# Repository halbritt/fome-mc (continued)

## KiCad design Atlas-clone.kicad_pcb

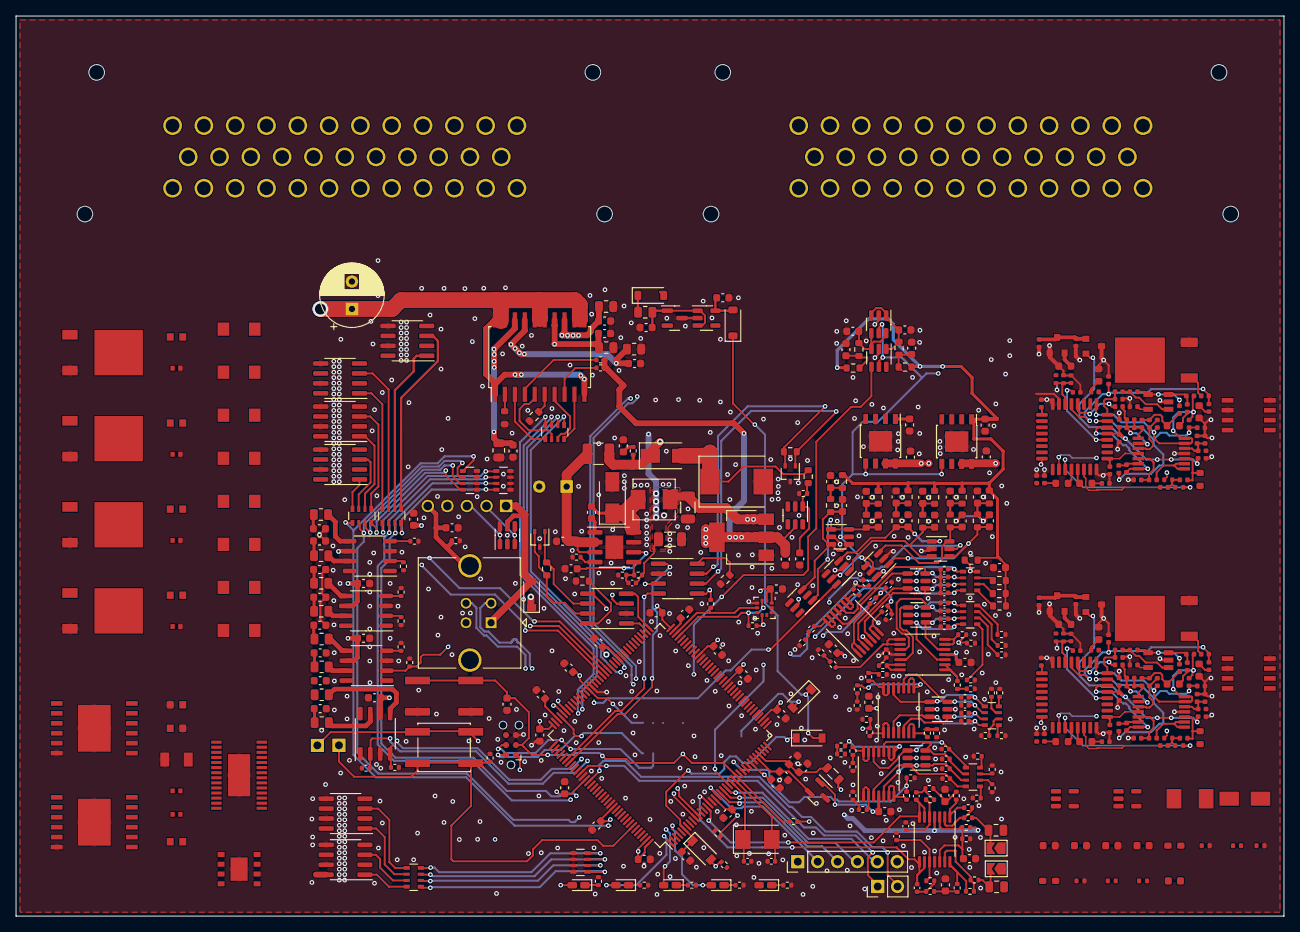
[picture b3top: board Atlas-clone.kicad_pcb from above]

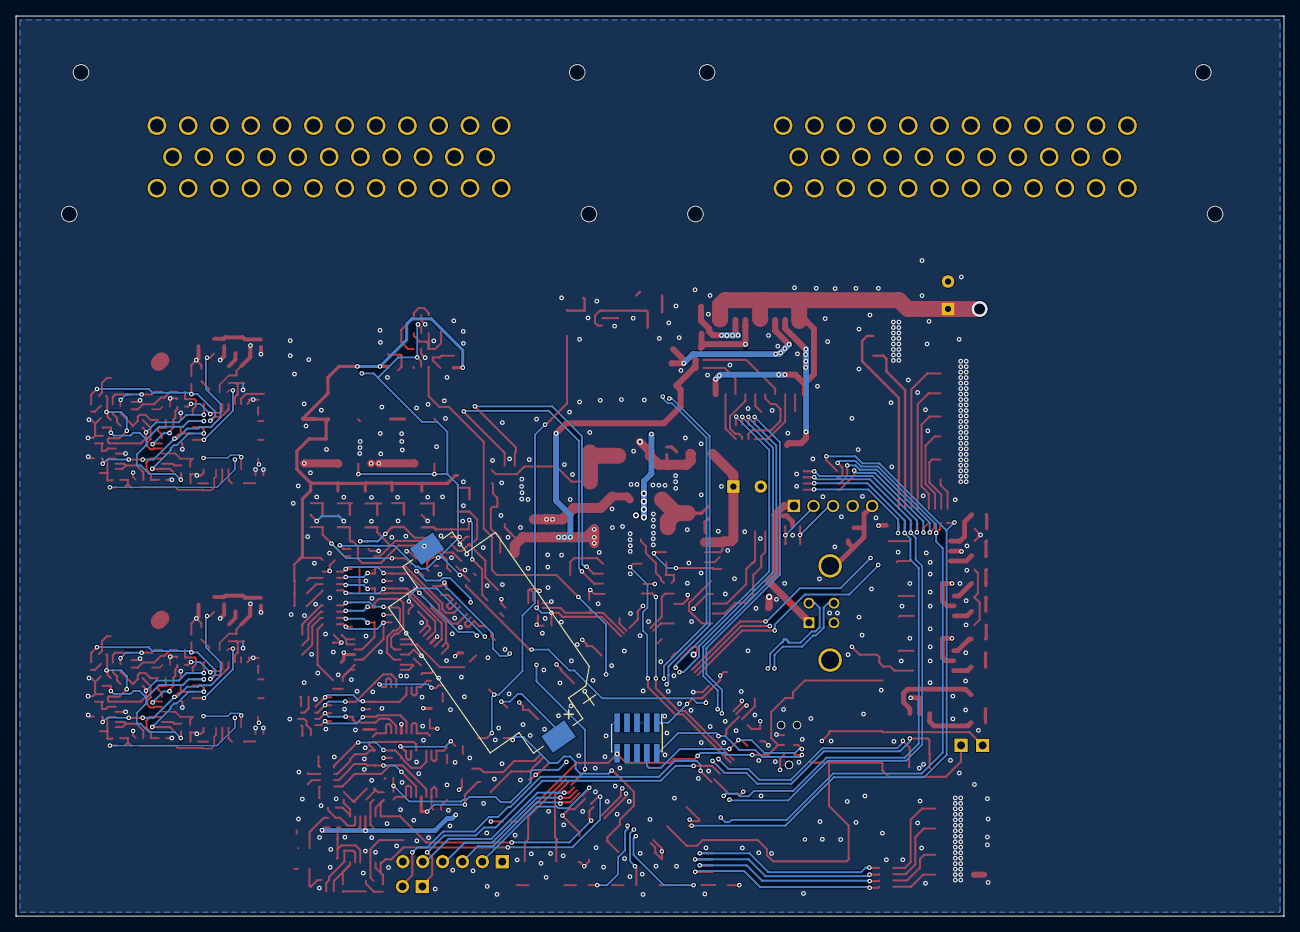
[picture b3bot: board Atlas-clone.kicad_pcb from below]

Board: 4 copper layers, 162.0 x 115.0 mm, 474 parts (2 on the bottom side), 353 nets.

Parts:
BT1: Battery_Cell; BatteryHolder_Keystone_1060_1x2032
C1, C6: 47u; CP_Elec_8x10.5
C2, C3, C5, C7, C9, C84: 1u; C_0603_1608Metric
C4, C14, C65, C66, C72, C76, C80, C82, C107, C310, C410: 4.7u; C_0603_1608Metric
C8, C15, C85, C86, C87, C88, C93, C94, C95, C96, C99, C100, C101, C102, C201, C202: 10n; C_0603_1608Metric
C10, C40, C41, C46, C51, C56, C61, C62, C63, C64, C67, C68, C69, C70, C71, C73, C79, C81, C83, C89, C91, C92, C97, C98, C103, C104, C105, C106: 100n; C_0603_1608Metric
C11, C20, C21: 330p; C_0402_1005Metric
C12, C13, C1201: 10u; C_1206_3216Metric
C16, C17: 3.3n; C_0805_2012Metric
C18, C19: 680p; C_0603_1608Metric
C22, C23: 47p; C_0402_1005Metric
C24, C25, C26, C27, C28, C29, C30, C31, C32, C33, C34, C35, C36, C37, C38, C39: 1n; C_0603_1608Metric
C42, C43, C44, C45, C47, C48, C49, C50, C52, C53, C54, C55, C57, C58, C59, C60, C302, C305, C308, C309, C311, C312, C313, C314, C316, C402, C405, C408, C409, C411, C412, C413, C414, C416: 100n; C_0402_1005Metric
C74, C75: 33p; C_0402_1005Metric
C77, C78, C90: 2.2u; C_0603_1608Metric
C301, C304, C306, C307, C317, C401, C404, C406, C407, C417: 1u; C_0402_1005Metric
C303, C403: 33n; C_0402_1005Metric
D1: SM15T33CA; D_SMC
D2, D3, D18: D_Schottky; D_SMA
D4, D5: PESD1CAN-UX; SOT-323_SC-70
D6, D7, D8, D14, D16, D17: schottky; D_SOD-123
D9, D12, D302, D402: GREEN; LED_0603_1608Metric
D10, D301, D304, D401, D404: RED; LED_0603_1608Metric
D11, D303, D403: BLUE; LED_0603_1608Metric
D13: ORANGE; LED_0603_1608Metric
D15: SRV05-4; SOT-23-6
D201, D202, D203, D204, D205, D206, D207, D208: B340A-13-F; D_SMA
FB1: Ferrite_Bead; L_0805_2012Metric
IC1: PSM712-LF-T7; SOT-23
J1: TE_776163-1; ampseal-35
J2: TE_776163-2; ampseal-35-2
J8: Conn_02x05_Odd_Even; PinHeader_2x05_P1.27mm_Vertical_SMD
J9: Conn_01x06; Tag-Connect_TC2030-IDC-NL_2x03_P1.27mm_Vertical
J11: Conn_01x06; PinHeader_1x06_P2.54mm_Vertical
J12: Conn_01x02; PinHeader_1x02_P2.54mm_Vertical
J13: USB_B; conn_5_2.5mm
J14: USB_B; USB_B_TE_5787834_Vertical
J15, J16: Conn_01x01; PinHeader_1x01_P2.54mm_Vertical
JP1, JP2: Jumper_NO_Small; SolderJumper-2_P1.3mm_Open_TrianglePad1.0x1.5mm
L1: 2.2u; L_1210_3225Metric
L2, L3: 10u; MWSA0503
Q201, Q202, Q203, Q204: FGD3040G2-F085; TO-252-2
Q301, Q401: VND14NV04; TO-252-2
R1, R3, R4, R47, R48, R49, R50, R59, R60, R61, R62, R71, R72, R73, R74, R83, R84, R85, R86, R89, R90, R97, R99, R100, R117, R118, R119, R121, R123, R205, R206, R207, R208, R209, R210, R303, R304, R311, R312, R321, R329, R333, R334, R403, R404, R411, R412, R421, R429, R433, R434: 10k; R_0402_1005Metric
R2: 1; R_0402_1005Metric
R5, R17, R18: 12k; R_0402_1005Metric
R6, R122, R331, R332, R431, R432: 68k; R_0402_1005Metric
R7, R8: 10; R_0603_1608Metric
R9, R10, R101, R102: 120; R_0603_1608Metric
R11, R12, R21, R22: 33k; R_0402_1005Metric
R13, R14, R19, R20, R98, R315, R317, R320, R415, R417, R420: 100k; R_0402_1005Metric
R15, R16, R51, R52, R53, R54, R63, R64, R65, R66, R75, R76, R77, R78: 470k; R_0402_1005Metric
R23, R24, R25, R26, R27, R28, R29, R30, R31, R32, R33, R34, R35, R36, R37, R38, R39, R40, R41, R42: 2.7k; R_0603_1608Metric
R43, R44, R45, R46, R55, R56, R57, R58, R67, R68, R69, R70, R79, R80, R81, R82: 5.6k; R_0402_1005Metric
R87, R88, R301, R302, R313, R318, R325, R326, R327, R330, R401, R402, R413, R418, R425, R426, R427, R430, R1501, R1502, R1503, R1504, R1601, R1602, R1603, R1604: 1k; R_0402_1005Metric
R91, R92, R93, R94, R95: 330; R_0402_1005Metric
R96, R116, R120: 82k; R_0603_1608Metric
R103, R104, R105, R106, R107: 4.7k; R_0805_2012Metric
R108, R109, R110, R111, R112, R113, R114, R115: 100; R_0805_2012Metric
R201, R202, R203, R204: 15R; R_0603_1608Metric
R212: 2.2k; R_0603_1608Metric
R305, R307, R405, R407: 27k; R_0402_1005Metric
R306, R406: 22k; R_0402_1005Metric
R308, R408: 47; R_0402_1005Metric
R309, R409: 10; R_0402_1005Metric
R310, R410: 61.9; R_0603_1608Metric
R314, R414: 62k; R_0603_1608Metric
R316, R416: 6.8k; R_0402_1005Metric
R319, R419: 47k; R_0402_1005Metric
R324, R424: 3.3k; R_0402_1005Metric
RN1, RN2, RN3, RN4, RN11: 10k; R_Array_Convex_4x0603
RN5, RN6, RN7, RN8, RN9, RN10: 1k; R_Array_Convex_4x0603
SW1, SW2: SW_Push; SW_SPST_EVQQ2
U1, U2: TLS115D0E; Infineon_PG-DSO-8-43
U3: LMR14020; SOIC-8-1EP_3.9x4.9mm_P1.27mm_EP2.29x3mm
U4, U5: MCP2551-I-SN; SOIC-8_3.9x4.9mm_P1.27mm
U6: AMS1117-3.3; SOT-223-3_TabPin2
U7, U15, U17, U19, U21, U301, U401: MCP6004; TSSOP-14_4.4x5mm_P0.65mm
U8, U9, U10, U14: SN74LVC2G17DB; SOT-23-6
U11, U12, U13, U16, U18, U20, U22: SRV05-4; SOT-23-6
U23: REF3333; SOT-23
U24: LPS25HB; ST_HLGA-10_2.5x2.5mm_P0.6mm_LayoutBorder3x2y
U25: XTSD04GLGEAG; LGA-8_6x8mm_P1.25mm
U26: STM32H753ZIT6; LQFP-144_20x20mm_P0.5mm
U27: USBLC6-2SC6; SOT-23-6
U28: S3225SMD32.768KOSC; SOT-23-5
U40: BTS716G; Infineon_PG-DSO-20-32
U41: MIC5205-3.3YM5; SOT-23-5
U42, U43, U44, U45: MIC4427; SO-8_3.9x4.9mm_P1.27mm
U46: LM2733XMFX/NOPB; SOT-23-5
U201, U203: TLE9201SG; Infineon_PG-DSO-12-9
U202: DRV8825PWPR; HTSSOP-28-1EP_4.4x9.7mm_P0.65mm_EP2.85x5.4mm
U302, U402: STM32F042K6Tx; LQFP-32_7x7mm_P0.8mm
U303, U403: REF3033; SOT-23
U305, U405: AD8628; TSOT-23-5
U307, U407: TJA1051T-3; SOIC-8_3.9x4.9mm_P1.27mm
U309, U409: XC6206P332MR; SOT-23
U1001, U1002, U1101, U1102, U1201, U1202: VNLD5090; SOIC-8_3.9x4.9mm_P1.27mm
Y1: 8MHz; Crystal_SMD_5032-2Pin_5.0x3.2mm

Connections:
+3.3V: R210.2, U201.2, U202.12, U202.16, U203.2
+3V3: C14.1, C61.2, C62.2, C63.1, C64.2, C65.2, C66.2, C67.2, C68.2, C69.2, C71.2, C72.2, C73.2, C76.2, D8.2 (A), D9.2 (A), D15.5 (VP), FB1.1, J8.1, J9.1, J11.1, J15.1, R1.2, R4.2, R11.2, R87.1, R88.1, R89.2, R99.2, R100.2, SW2.2, U4.5 (Vref), U5.5 (Vref), U6.2 (VO), U7.4 (V+), U24.1 (VDDio), U24.6 (~CS), U24.10 (VDD), U25.4, U26.17 (VDD), U26.30 (VDD), U26.39 (VDD), U26.52 (VDD), U26.62 (VDD), U26.72 (VDD), U26.84 (VDD), U26.95 (VDDUSB), U26.108 (VDD), U26.121 (VDDSDMMC), U26.131 (VDD), U26.143 (PDR_ON), U26.144 (VDD)
+3V3_WBO1: C305.1, C310.1, C312.1, C313.1, C314.1, R314.1, R318.2, U301.4 (V+), U302.1 (VDD), U302.17 (VDDIO2), U305.5 (V+), U309.2 (VO)
+3V3_WBO2: C405.1, C410.1, C412.1, C413.1, C414.1, R414.1, R418.2, U401.4 (V+), U402.1 (VDD), U402.17 (VDDIO2), U405.5 (V+), U409.2 (VO)
+5V: C11.1, C12.1, C13.1, C40.1, C46.1, C51.1, C56.1, C91.2, C92.2, C97.2, C98.2, C308.1, C317.1, C408.1, C417.1, D14.1 (K), L2.2, R6.2, U1.5 (ADJ), U2.5 (ADJ), U4.3 (VDD), U5.3 (VDD), U6.3 (VI), U8.5 (VCC), U9.5 (VCC), U10.5 (VCC), U11.5 (VP), U12.5 (VP), U13.5 (VP), U14.5 (VCC), U15.4 (V+), U16.5 (VP), U17.4 (V+), U18.5 (VP), U19.4 (V+), U20.5 (VP), U21.4 (V+), U22.5 (VP), U23.1 (IN), U42.6 (V+), U43.6 (V+), U44.6 (V+), U45.6 (V+), U303.1 (IN), U307.3, U309.3 (VI), U403.1 (IN), U407.3, U409.3 (VI)
/5V_SENSOR_1: C3.1, C41.2, J1.29, R23.1, R24.1, R25.1, R26.1, R27.1, R28.1, R35.1, R36.1, R39.1, R40.1, R41.1, R42.1, R118.1, U1.1 (OUT)
/5V_SENSOR_2: C9.1, J1.30, U2.1 (OUT)
/12V_MR: C1.1, C1201.2, D201.1, D202.1, D203.1, D204.1, D205.1, D206.1, D207.1, D208.1, J1.24, J1.27, R116.1, R212.1, R320.1, R420.1, U40.1 (VBB), U40.10 (VBB), U40.11 (VBB), U40.12 (VBB), U40.15 (VBB), U40.16 (VBB), U40.19 (VBB), U40.20 (VBB), U201.4, U202.11, U203.4
/12V_PROT: C2.1, C5.1, D2.1 (K), L1.1, R2.1, U1.7 (EN), U1.8 (IN), U2.7 (EN), U2.8 (IN)
/12V_RAW: D1.1 (A1), D2.2 (A), J1.26, R96.1
/AT1: J2.1, R39.2, RN1.1 (R1.1)
/AT2: J2.2, R40.2, RN1.2 (R2.1)
/AT3: R41.2, RN1.3 (R3.1)
/AT4: R42.2, RN1.4 (R4.1)
/AV1: J2.5, R51.1, RN2.1 (R1.1)
/AV2: J2.3, R52.1, RN2.2 (R2.1)
/AV3: J2.6, R53.1, RN2.3 (R3.1)
/AV4: J2.4, R54.1, RN2.4 (R4.1)
/AV5: J2.7, R63.1, RN3.1 (R1.1)
/AV6: J2.8, R64.1, RN3.2 (R2.1)
/AV7: R65.1, RN3.3 (R3.1)
/AV8: R66.1, RN3.4 (R4.1)
/AV9: R75.1, RN4.1 (R1.1)
/AV10: R76.1, RN4.2 (R2.1)
/AV11: R77.1, RN4.3 (R3.1)
/BOOT0_NET: J16.1, R90.1, R209.2, SW2.1, U26.138 (BOOT0)
/CAN2+: D5.2 (A2), R10.1, U5.7 (CANH), U307.7, U407.7
/CAN2-: D5.1 (A1), R10.2, U5.6 (CANL), U307.6, U407.6
/CAN+: D4.2 (A2), J2.28, R9.1, U4.7 (CANH)
/CAN-: D4.1 (A1), J2.29, R9.2, U4.6 (CANL)
/DIGITAL_1: C24.1, J2.16, R23.2, R29.2
/DIGITAL_2: C25.1, J2.15, R24.2, R30.2
/DIGITAL_3: C26.1, J2.18, R25.2, R31.2
/DIGITAL_4: C27.1, J2.17, R26.2, R32.2
/DIGITAL_5: C28.1, R27.2, R33.2
/DIGITAL_6: C29.1, R28.2, R34.2
/ETB1_DIR: U26.79 (PD10), U201.1
/ETB1_DIS: R210.1, U26.80 (PD11), U201.11
/ETB1_OUT+: C201.2, J1.15, U201.5
/ETB1_OUT-: C202.1, J1.16, U201.7
/ETB1_PWM: U26.81 (PD12), U201.12
/ETB2_DIR: U26.78 (PD9), U203.1
/ETB2_DIS: U26.77 (PD8), U203.11
/ETB2_OUT+: J1.17, U203.5
/ETB2_OUT-: J1.18, U203.7
/ETB2_PWM: U26.82 (PD13), U203.12
/HS1: C85.1, J1.14, R103.1, U40.18 (OUT1)
/HS2: C86.1, R104.1, U40.17 (OUT2)
/HS3: C87.1, R105.1, U40.14 (OUT3)
/HS4: C88.1, R106.1, U40.13 (OUT4)
/IGN1: C93.1, R108.1, R201.1
/IGN1_COIL: J1.6, Q201.2
/IGN2: C94.1, R109.1, R202.1
/IGN2_COIL: J1.7, Q202.2
/IGN3: C95.1, R110.1, R203.1
/IGN3_COIL: J1.8, Q203.2
/IGN4: C96.1, R111.1, R204.1
/IGN4_COIL: J1.9, Q204.2
/IGN5: C99.1, J2.23, R112.1
/IGN6: C100.1, J2.24, R113.1
/IGN7: C101.1, J2.25, R114.1
/IGN8: C102.1, J2.26, R115.1
/IGN10: J12.2, U26.122 (PD6)
/IGN11: J12.1, U26.119 (PD5)
/KNOCK_1: C16.2, J2.9, JP1.1
/KNOCK_2: C17.2, J2.10, JP2.1
/Keep_Alive/Keep_Alive: D6.1 (K), D7.2 (A), D17.1 (K)
/LS1: D201.2, J1.1, U1001.6 (D2)
/LS2: D202.2, J1.2, U1001.8 (D1)
/LS3: D203.2, J1.3, U1002.6 (D2)
/LS4: D204.2, J1.4, U1002.8 (D1)
/LS5: D205.2, J1.10, U1101.6 (D2)
/LS6: D206.2, J1.11, U1101.8 (D1)
/LS7: D207.2, J1.12, U1102.6 (D2)
/LS8: D208.2, J1.13, U1102.8 (D1)
/LS9: U26.134 (PB4), U202.22
/LS12: U26.137 (PB7), U202.20
/LS14: J2.27, R212.2, U1201.8 (D1)
/PB8_STEP_EN: RN9.8 (R1.2), RN10.4 (R4.1), U26.139 (PB8), U202.21
/Perm_Live: D16.2 (A), J1.28
/RC2: J1.35, R209.1, U26.101 (PA9)
/STEP_1A: J1.19, U202.4
/STEP_1B: J1.20, U202.6
/STEP_2A: J1.21, U202.9
/STEP_2B: J1.22, U202.7
/USB_D+: J2.34, J13.3, J14.3, U26.104 (PA12), U27.1 (I/O1), U27.6 (I/O1)
/USB_D-: J2.35, J13.2, J14.2, U26.103 (PA11), U27.3 (I/O2), U27.4 (I/O2)
/USB_SHIELD: C83.1, J13.5, J14.5, R98.1
/VBOOST: C6.1, C7.1, L1.2, R120.1, U3.2 (VIN), U3.3 (EN)
/VR1+: C37.1, J2.11, R36.2, R38.2
/VR2+: C36.1, J2.13, R35.2, R37.2
/WBO1_BOOT0: R329.2, U26.2 (PE3), U302.31 (PB8)
/WBO1_H-: J1.23, Q301.2 (D)
/WBO1_IP: J2.20, R310.2, R312.2
/WBO1_NRST: C316.1, U26.1 (PE2), U302.4 (NRST)
/WBO1_RTRIM: J2.21, R308.1, R310.1, R311.2, R334.1
/WBO1_UN: C302.1, J2.22, R314.2, U301.10 (+)
/WBO1_VM: C304.1, J2.19, R303.1, R309.1, U302.7 (PA1)
/WBO2_BOOT0: R429.2, U26.4 (PE5), U402.31 (PB8)
/WBO2_H-: J1.25, Q401.2 (D)
/WBO2_IP: J2.31, R410.2, R412.2
/WBO2_NRST: C416.1, U26.3 (PE4), U402.4 (NRST)
/WBO2_RTRIM: J2.32, R408.1, R410.1, R411.2, R434.1
/WBO2_UN: C402.1, J2.33, R414.2, U401.10 (+)
/WBO2_VM: C404.1, J2.30, R403.1, R409.1, U402.7 (PA1)
/highside_quad/IN1: RN11.4 (R4.1), U26.89 (PG4)
/highside_quad/IN2: RN11.3 (R3.1), U26.88 (PG3)
/highside_quad/IN3: RN11.2 (R2.1), U26.87 (PG2)
/highside_quad/IN4: RN11.1 (R1.1), U26.86 (PD15)
/ign1/IN1: R1501.2, U26.133 (PB3), U42.2 (IN_A)
/ign1/IN2: R1502.2, U26.132 (PG15), U42.4 (IN_B)
/ign1/IN3: R1503.2, U26.129 (PG14), U43.2 (IN_A)
/ign1/IN4: R1504.2, U26.128 (PG13), U43.4 (IN_B)
/ign2/IN1: R1601.2, U26.127 (PG12), U44.2 (IN_A)
/ign2/IN2: R1602.2, U26.126 (PG11), U44.4 (IN_B)
/ign2/IN3: R1603.2, U26.125 (PG10), U45.2 (IN_A)
/ign2/IN4: R1604.2, U26.124 (PG9), U45.4 (IN_B)
/knock/FILTERED_1: C20.2, U7.6 (-), U7.7, U26.14 (PF4)
/knock/FILTERED_2: C21.2, U7.8, U7.9 (-), U26.15 (PF5)
/knock/V_mid: C15.2, R11.1, R12.1, U7.3 (+), U7.12 (+)
/lowside_quad1/IN1: RN5.8 (R1.2), RN6.4 (R4.1), U26.90 (PG5)
/lowside_quad1/IN2: RN5.7 (R2.2), RN6.3 (R3.1), U26.91 (PG6)
/lowside_quad1/IN3: RN5.6 (R3.2), RN6.2 (R2.1), U26.92 (PG7)
/lowside_quad1/IN4: RN5.5 (R4.2), RN6.1 (R1.1), U26.93 (PG8)
/lowside_quad2/IN1: RN7.8 (R1.2), RN8.4 (R4.1), U26.96 (PC6)
/lowside_quad2/IN2: RN7.7 (R2.2), RN8.3 (R3.1), U26.97 (PC7)
/lowside_quad2/IN3: RN7.6 (R3.2), RN8.2 (R2.1), U26.110 (PA15)
/lowside_quad2/IN4: RN7.5 (R4.2), RN8.1 (R1.1), U26.117 (PD3)
/lowside_quad4/IN2: RN9.7 (R2.2), RN10.3 (R3.1), U26.140 (PB9)
/lowside_quad4/IN3: RN9.6 (R3.2), RN10.2 (R2.1), U26.141 (PE0)
/lowside_quad4/IN4: RN9.5 (R4.2), RN10.1 (R1.1), U26.142 (PE1)
/mcu/5V_SENSE_DIVIDED: C104.1, R118.2, R119.1, U26.50 (PF12)
/mcu/5V_SENSOR_1_PG: R1.1, U1.4 (PG), U26.55 (PF15)
/mcu/5V_SENSOR_2_PG: R4.1, U2.4 (PG), U26.54 (PF14)
/mcu/12V_DIVIDED: C84.1, D15.1 (IO1), R96.2, R97.1, U26.45 (PC5)
/mcu/AT1: R43.1, R47.2, U26.27 (PC1)
/mcu/AT2: R44.1, R48.2, U26.28 (PC2)
/mcu/AT3: R45.1, R49.2, U26.29 (PC3)
/mcu/AT4: R46.1, R50.2, U26.44 (PC4)
/mcu/AUX_SPI_CS: J11.2, U26.18 (PF6)
/mcu/AUX_SPI_MISO: J11.4, U26.20 (PF8)
/mcu/AUX_SPI_MOSI: J11.5, U26.21 (PF9)
/mcu/AUX_SPI_SCK: J11.3, U26.19 (PF7)
/mcu/AV1: R55.1, R59.2, U26.34 (PA0)
/mcu/AV2: R56.1, R60.2, U26.35 (PA1)
/mcu/AV3: R57.1, R61.2, U26.36 (PA2)
/mcu/AV4: R58.1, R62.2, U26.37 (PA3)
/mcu/AV5: R67.1, R71.2, U26.40 (PA4)
/mcu/AV6: R68.1, R72.2, U26.41 (PA5)
/mcu/AV7: R69.1, R73.2, U26.42 (PA6)
/mcu/AV8: R70.1, R74.2, U26.43 (PA7)
/mcu/AV9: R79.1, R83.2, U26.46 (PB0)
/mcu/AV10: R80.1, R84.2, U26.47 (PB1)
/mcu/AV11: R81.1, R85.2, U26.26 (PC0)
/mcu/BARO_SCL: R88.2, U24.2 (SCL/SCLK), U26.69 (PB10)
/mcu/BARO_SDA: R87.2, U24.4 (SDA/MOSI), U26.70 (PB11)
/mcu/CAN2_RX: U5.4 (RXD), U26.73 (PB12)
/mcu/CAN2_TX: U5.1 (TXD), U26.74 (PB13)
/mcu/CAN_RX: U4.4 (RXD), U26.114 (PD0)
/mcu/CAN_TX: U4.1 (TXD), U26.115 (PD1)
/mcu/DIGITAL1: U10.6, U26.56 (PG0)
/mcu/DIGITAL2: U8.6, U26.57 (PG1)
/mcu/DIGITAL3: U8.4, U26.63 (PE10)
/mcu/DIGITAL4: U9.6, U26.64 (PE11)
/mcu/DIGITAL5: U10.4, U26.65 (PE12)
/mcu/DIGITAL6: U9.4, U26.66 (PE13)
/mcu/LED1: D10.2 (A), U26.10 (PF0)
/mcu/LED2: D11.2 (A), U26.12 (PF2)
/mcu/LED3: D12.2 (A), U26.85 (PD14)
/mcu/LED4: D13.2 (A), U26.11 (PF1)
/mcu/MR_DIVIDED: C103.1, R116.2, R117.1, U26.49 (PF11)
/mcu/SD_CLK: U25.5, U26.113 (PC12)
/mcu/SD_CMD: U25.3, U26.116 (PD2)
/mcu/SD_D0: U25.7, U26.98 (PC8)
/mcu/SD_D1: U25.8, U26.99 (PC9)
/mcu/SD_D2: U25.1, U26.111 (PC10)
/mcu/SD_D3: U25.2, U26.112 (PC11)
/mcu/SWCLK: J8.4, J9.4, U26.109 (PA14)
/mcu/SWDIO: J8.2, J9.2, U26.105 (PA13)
/mcu/VBOOST_DIVIDED: C105.1, R120.2, R121.1, U26.53 (PF13)
/mcu/VDDA: C81.1, C82.1, FB1.2, U26.33 (VDDA)
/mcu/VR_1: U14.6, U26.67 (PE14)
/mcu/VR_2: U14.4, U26.68 (PE15)
/mcu/nRESET: C79.2, J8.10, J9.3, R89.1, SW1.1, U26.25 (NRST)
/quad_analog3/IN4: R78.1, RN4.4 (R4.1)
/quad_analog3/OUT4: R82.1, R86.2
/wbo1/CAN_RX: U302.21 (PA11), U307.4
/wbo1/CAN_TX: U302.22 (PA12), U307.1
/wbo1/Ip_dac: R331.1, U302.12 (PA6)
/wbo1/Ip_sense: C311.1, R324.2, U302.8 (PA2)
/wbo1/LED_BLUE: D303.2 (A), U302.28 (PB5)
/wbo1/LED_GREEN: D302.2 (A), U302.29 (PB6)
/wbo1/LSU_Un_sense: R304.1, U301.8, U301.9 (-)
/wbo1/Nernst_esr_drive_42: R316.2, U302.26 (PB3)
/wbo1/Nernst_esr_drive_49: R306.2, U302.30 (PB7)
/wbo1/Nernst_esr_drive_adv: R319.2, U302.27 (PB4)
/wbo1/Un_sense: R307.2, U301.7, U302.6 (PA0)
/wbo1/Vm: R309.2, R315.2, R332.2, U301.13 (-), U301.14, U302.9 (PA3)
/wbo1/heater_pwm: R325.2, R326.2, R327.2, U302.13 (PA7)
/wbo2/+3V3: U402.18 (PA8), U407.5
/wbo2/CAN_RX: U402.21 (PA11), U407.4
/wbo2/CAN_TX: U402.22 (PA12), U407.1
/wbo2/Ip_dac: R431.1, U402.12 (PA6)
/wbo2/Ip_sense: C411.1, R424.2, U402.8 (PA2)
/wbo2/LED_BLUE: D403.2 (A), U402.28 (PB5)
/wbo2/LED_GREEN: D402.2 (A), U402.29 (PB6)
/wbo2/LSU_Un_sense: R404.1, U401.8, U401.9 (-)
/wbo2/Nernst_esr_drive_42: R416.2, U402.26 (PB3)
/wbo2/Nernst_esr_drive_49: R406.2, U402.30 (PB7)
/wbo2/Nernst_esr_drive_adv: R419.2, U402.27 (PB4)
/wbo2/Un_sense: R407.2, U401.7, U402.6 (PA0)
/wbo2/Vm: R409.2, R415.2, R432.2, U401.13 (-), U401.14, U402.9 (PA3)
/wbo2/heater_pwm: R425.2, R426.2, R427.2, U402.13 (PA7)
GND: BT1.2 (-), C1.2, C2.2, C3.2, C4.2, C5.2, C6.2, C7.2, C8.2, C9.2, C12.2, C13.2, C14.2, C15.1, C18.1, C19.1, C22.1, C23.1, C24.2, C25.2, C26.2, C27.2, C28.2, C29.2, C30.2, C31.2, C32.2, C33.2, C34.2, C35.2, C36.2, C37.2, C38.2, C39.2, C40.2, C41.1, C42.2, C43.2, C44.2, C45.2, C46.2, C47.2, C48.2, C49.2, C50.2, C51.2, C52.2, C53.2, C54.2, C55.2, C56.2, C57.2, C58.2, C59.2, C60.2, C61.1, C62.1, C63.2, C64.1, C65.1, C66.1, C67.1, C68.1, C69.1, C70.2, C71.1, C72.1, C73.1, C74.2, C75.2, C76.1, C77.2, C78.2, C79.1, C80.2, C81.2, C82.2, C83.2, C84.2, C85.2, C86.2, C87.2, C88.2, C89.2, C90.1, C91.1, C92.1, C93.2, C94.2, C95.2, C96.2, C97.1, C98.1, C99.2, C100.2, C101.2, C102.2, C103.2, C104.2, C105.2, C201.1, C202.2, C301.2, C304.2, C305.2, C306.2, C307.2, C308.2, C309.2, C310.2, C311.2, C312.2, C313.2, C314.2, C316.2, C317.2, C401.2, C404.2, C405.2, C406.2, C407.2, C408.2, C409.2, C410.2, C411.2, C412.2, C413.2, C414.2, C416.2, C417.2, C1201.1, D1.2 (A2), D3.2 (A), D4.3 (common), D5.3 (common), D15.2 (VN), D301.1 (K), D304.1 (K), D401.1 (K), D404.1 (K), IC1.3 (GND), J1.5, J1.31, J1.32, J1.33, J1.34, J2.12, J2.14, J8.3, J8.5, J8.9, J9.5, J11.6, J13.4, J14.4, Q201.3, Q202.3, Q203.3, Q204.3, Q301.3 (S), Q401.3 (S), R3.2, R5.2, R7.1, R8.1, R12.2, R47.1, R48.1, R49.1, R50.1, R51.2, R52.2, R53.2, R54.2, R59.1, R60.1, R61.1, R62.1, R63.2, R64.2, R65.2, R66.2, R71.1, R72.1, R73.1, R74.1, R75.2, R76.2, R77.2, R78.2, R83.1, R84.1, R85.1, R86.1, R90.2, R91.1, R92.1, R93.1, R94.1, R95.1, R97.2, R98.2, R101.2, R102.2, R103.2, R104.2, R105.2, R106.2, R117.2, R119.2, R121.2, R205.2, R206.2, R207.2, R208.2, R302.2, R305.2, R313.1, R321.2, R326.1, R329.1, R330.1, R402.2, R405.2, R413.1, R421.2, R426.1, R429.1, R430.1, R1501.1, R1502.1, R1503.1, R1504.1, R1601.1, R1602.1, R1603.1, R1604.1, RN5.1 (R1.1), RN5.2 (R2.1), RN5.3 (R3.1), RN5.4 (R4.1), RN7.1 (R1.1), RN7.2 (R2.1), RN7.3 (R3.1), RN7.4 (R4.1), RN9.1 (R1.1), RN9.2 (R2.1), RN9.3 (R3.1), RN9.4 (R4.1), SW1.2, U1.3 (GND), U1.9 (GND), U2.3 (GND), U2.9 (GND), U3.7 (GND), U3.9 (GND), U4.2 (VSS), U5.2 (VSS), U6.1 (GND), U7.11 (V-), U8.2 (GND), U9.2 (GND), U10.2 (GND), U11.2 (VN), U12.2 (VN), U13.2 (VN), U14.2 (GND), U15.11 (V-), U16.2 (VN), U17.11 (V-), U18.2 (VN), U19.11 (V-), U20.2 (VN), U21.11 (V-), U22.2 (VN), U23.3 (GND), U24.3 (GND), U24.5 (SA0/MISO), U24.8 (GND), U24.9 (GND), U25.6, U25.9, U26.16 (VSS), U26.31 (VSSA), U26.38 (VSS), U26.48 (PB2), U26.51 (VSS), U26.61 (VSS), U26.83 (VSS), U26.94 (VSS), U26.107 (VSS), U26.120 (VSS), U26.130 (VSS), U27.2 (GND), U41.2 (GND), U42.3 (GND), U43.3 (GND), U44.3 (GND), U45.3 (GND), U201.6, U201.13, U202.29, U203.6, U203.13, U301.11 (V-), U302.15 (PB1), U302.16 (VSS), U302.32 (VSSA), U303.3 (GND), U305.2 (V-), U307.2, U307.8, U309.1 (GND), U401.11 (V-), U402.16 (VSS), U402.32 (VSSA), U403.3 (GND), U405.2 (V-), U407.2, U407.8, U409.1 (GND), U1001.5 (S2), U1001.7 (S1), U1002.5 (S2), U1002.7 (S1), U1101.5 (S2), U1101.7 (S1), U1102.5 (S2), U1102.7 (S1), U1201.5 (S2), U1201.7 (S1), U1202.5 (S2), U1202.7 (S1)
unnamed: BT1.1 (+), D6.2 (A)
unnamed: C4.1, R2.2
unnamed: C16.1, JP1.2, R13.2
unnamed: C17.1, JP2.2, R14.2
unnamed: C18.2, R17.1, R19.2
unnamed: C19.2, R18.1, R20.2
unnamed: C20.1, R19.1, R21.2
unnamed: C21.1, R20.1, R22.2
unnamed: C302.2, R306.1, R316.1, R319.1
unnamed: C303.1, R308.2, R333.1, U301.1
unnamed: C402.2, R406.1, R416.1, R419.1
unnamed: C403.1, R408.2, R433.1, U401.1
unnamed: C10.2, D3.1 (K), L2.1, U3.8 (SW)
unnamed: C80.1, D7.1 (K), D8.1 (K), U26.6 (VBAT)
unnamed: D9.1 (K), R91.2
unnamed: D10.1 (K), R92.2
unnamed: D11.1 (K), R93.2
unnamed: D12.1 (K), R94.2
unnamed: D13.1 (K), R95.2
unnamed: D14.2 (A), J13.1, J14.1, U27.5 (VBUS)
unnamed: D16.1 (K), R107.1
unnamed: C90.2, D17.2 (A), U41.5 (OUT)
unnamed: D18.2 (A), L3.2
unnamed: D301.2 (A), R327.1
unnamed: D302.1 (K), R330.2
unnamed: D303.1 (K), R313.2
unnamed: D304.2 (A), R318.1
unnamed: D401.2 (A), R427.1
unnamed: D402.1 (K), R430.2
unnamed: D403.1 (K), R413.2
unnamed: D404.2 (A), R418.1
unnamed: C89.1, IC1.1 (I/O_1), R107.2, U41.1 (IN), U41.3 (EN)
unnamed: Q201.1, R201.2, R205.1
unnamed: Q202.1, R202.2, R206.1
unnamed: Q203.1, R203.2, R207.1
unnamed: Q204.1, R204.2, R208.1
unnamed: Q301.1 (G), R325.1
unnamed: Q401.1 (G), R425.1
unnamed: R15.1, R17.2, U7.1
unnamed: R16.1, R18.2, U7.14
unnamed: R317.1, R324.1, U305.1
unnamed: R417.1, R424.1, U405.1
unnamed: C42.1, RN1.8 (R1.2), U15.3 (+), U16.6 (IO4)
unnamed: C43.1, RN1.7 (R2.2), U15.5 (+), U16.1 (IO1)
unnamed: C44.1, RN1.6 (R3.2), U15.10 (+), U16.3 (IO2)
unnamed: C45.1, RN1.5 (R4.2), U15.12 (+), U16.4 (IO3)
unnamed: C47.1, RN2.8 (R1.2), U17.3 (+), U18.6 (IO4)
unnamed: C48.1, RN2.7 (R2.2), U17.5 (+), U18.1 (IO1)
unnamed: C49.1, RN2.6 (R3.2), U17.10 (+), U18.3 (IO2)
unnamed: C50.1, RN2.5 (R4.2), U17.12 (+), U18.4 (IO3)
unnamed: C52.1, RN3.8 (R1.2), U19.3 (+), U20.6 (IO4)
unnamed: C53.1, RN3.7 (R2.2), U19.5 (+), U20.1 (IO1)
unnamed: C54.1, RN3.6 (R3.2), U19.10 (+), U20.3 (IO2)
unnamed: C55.1, RN3.5 (R4.2), U19.12 (+), U20.4 (IO3)
unnamed: C57.1, RN4.8 (R1.2), U21.3 (+), U22.6 (IO4)
unnamed: C58.1, RN4.7 (R2.2), U21.5 (+), U22.1 (IO1)
unnamed: C59.1, RN4.6 (R3.2), U21.10 (+), U22.3 (IO2)
unnamed: C60.1, RN4.5 (R4.2), U21.12 (+), U22.4 (IO3)
unnamed: RN6.8 (R1.2), U1002.1 (IN1)
unnamed: RN6.7 (R2.2), U1002.3 (IN2)
unnamed: RN6.6 (R3.2), U1001.1 (IN1)
unnamed: RN6.5 (R4.2), U1001.3 (IN2)
unnamed: RN8.8 (R1.2), U1102.1 (IN1)
unnamed: RN8.7 (R2.2), U1102.3 (IN2)
unnamed: RN8.6 (R3.2), U1101.1 (IN1)
unnamed: RN8.5 (R4.2), U1101.3 (IN2)
unnamed: RN10.8 (R1.2), U1202.1 (IN1)
unnamed: RN10.7 (R2.2), U1202.3 (IN2)
unnamed: RN10.6 (R3.2), U1201.1 (IN1)
unnamed: RN10.5 (R4.2), U1201.3 (IN2)
unnamed: RN11.8 (R1.2), U40.9 (IN4)
unnamed: RN11.7 (R2.2), U40.7 (IN3)
unnamed: RN11.6 (R3.2), U40.5 (IN2)
unnamed: RN11.5 (R4.2), U40.3 (IN1)
unnamed: C10.1, U3.1 (BOOT)
unnamed: C11.2, R5.1, R6.1, U3.5 (FB)
unnamed: R3.1, U3.4 (RT)
unnamed: C8.1, U3.6 (SS)
unnamed: R7.2, U4.8 (Rs)
unnamed: R8.2, U5.8 (Rs)
unnamed: R13.1, R15.2, U7.2 (-)
unnamed: C22.2, R21.1, U7.5 (+)
unnamed: C23.2, R22.1, U7.10 (+)
unnamed: R14.1, R16.2, U7.13 (-)
unnamed: C33.1, R32.1, U9.1, U11.1 (IO1), U11.6 (IO4)
unnamed: C35.1, R34.1, U9.3, U11.3 (IO2), U11.4 (IO3)
unnamed: C34.1, R33.1, U10.3, U12.1 (IO1)
unnamed: C30.1, R29.1, U10.1, U12.3 (IO2)
unnamed: C31.1, R30.1, U8.1, U12.4 (IO3)
unnamed: C32.1, R31.1, U8.3, U12.6 (IO4)
unnamed: C39.1, R38.1, U13.1 (IO1), U13.3 (IO2), U14.1
unnamed: C38.1, R37.1, U13.4 (IO3), U13.6 (IO4), U14.3
unnamed: R43.2, U15.1, U15.2 (-)
unnamed: R44.2, U15.6 (-), U15.7
unnamed: R45.2, U15.8, U15.9 (-)
unnamed: R46.2, U15.13 (-), U15.14
unnamed: R55.2, U17.1, U17.2 (-)
unnamed: R56.2, U17.6 (-), U17.7
unnamed: R57.2, U17.8, U17.9 (-)
unnamed: R58.2, U17.13 (-), U17.14
unnamed: R67.2, U19.1, U19.2 (-)
unnamed: R68.2, U19.6 (-), U19.7
unnamed: R69.2, U19.8, U19.9 (-)
unnamed: R70.2, U19.13 (-), U19.14
unnamed: R79.2, U21.1, U21.2 (-)
unnamed: R80.2, U21.6 (-), U21.7
unnamed: R81.2, U21.8, U21.9 (-)
unnamed: R82.2, U21.13 (-), U21.14
unnamed: C70.1, U23.2 (OUT), U26.32 (VREF+)
unnamed: C74.1, U26.23 (PH0), Y1.1
unnamed: C75.1, U26.24 (PH1), Y1.2
unnamed: C77.1, U26.71 (VCAP_1)
unnamed: C78.1, U26.106 (VCAP_2)
unnamed: C106.1, U28.2 (GND)
unnamed: R101.1, U40.2 (GND1/2)
unnamed: R102.1, U40.6 (GND3/4)
unnamed: R99.1, U40.4 (ST1/2)
unnamed: R100.1, U40.8 (ST3/4)
unnamed: R108.2, U42.7 (OUT_A)
unnamed: R109.2, U42.5 (OUT_B)
unnamed: R110.2, U43.7 (OUT_A)
unnamed: R111.2, U43.5 (OUT_B)
unnamed: R112.2, U44.7 (OUT_A)
unnamed: R113.2, U44.5 (OUT_B)
unnamed: R114.2, U45.7 (OUT_A)
unnamed: R115.2, U45.5 (OUT_B)
unnamed: C107.2, U46.1 (IN)
unnamed: R122.1, U46.5 (OUT)
unnamed: C301.1, R301.2, R302.1, R304.2, R305.1, R332.1, R334.2, U301.3 (+), U301.5 (+), U301.12 (+)
unnamed: C303.2, R303.2, R307.1, R331.2, R333.2, U301.2 (-), U301.6 (-)
unnamed: C306.1, R320.2, R321.1, U302.14 (PB0)
unnamed: R312.1, R315.1, U305.3 (+)
unnamed: R311.1, R317.2, U305.4 (-)
unnamed: C401.1, R401.2, R402.1, R404.2, R405.1, R432.1, R434.2, U401.3 (+), U401.5 (+), U401.12 (+)
unnamed: C403.2, R403.2, R407.1, R431.2, R433.2, U401.2 (-), U401.6 (-)
unnamed: C406.1, R420.2, R421.1, U402.14 (PB0)
unnamed: R412.1, R415.1, U405.3 (+)
unnamed: R411.1, R417.2, U405.4 (-)
VDDA: C307.1, C309.1, C407.1, C409.1, R301.1, R401.1, U302.5 (VDDA), U303.2 (OUT), U402.5 (VDDA), U403.2 (OUT)

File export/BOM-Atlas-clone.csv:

Comment,Designator,Footprint,LCSC
Ferrite_Bead,FB1,L_0805_2012Metric,C1015
SN74LVC2G17DB,"U10,U14,U8,U9",SOT-23-6,C10429
USBLC6-2SC6,U27,SOT-23-6,C111212
8MHz,Y1,Crystal_SMD_5032-2Pin_5.0x3.2mm,C115962
1k,"R1501,R1502,R1503,R1504,R1601,R1602,R1603,R1604,R87,R88",R_0402_1005Metric,C11702
REF3333,U23,SOT-23,C130016
2.7k,"R23,R24,R25,R26,R27,R28,R29,R30,R31,R32,R33,R34,R35,R36,R37,R38,R39,R40,R41,R42",R_0603_1608Metric,C13167
330p,"C11,C20,C21",C_0402_1005Metric,C13533
10u,"C12,C13",C_1206_3216Metric,C13585
100n,"C10,C40,C41,C46,C51,C56,C61,C62,C63,C64,C67,C68,C69,C70,C71,C73,C79,C81,C83,C89,C91,C92,C97,C98,C103,C104,C105,C106",C_0603_1608Metric,C14663
SM15T33CA,D1,D_SMC,C151281
100n,"C42,C43,C44,C45,C47,C48,C49,C50,C52,C53,C54,C55,C57,C58,C59,C60",C_0402_1005Metric,C1525
PESD1CAN-UX,"D4,D5",SOT-323_SC-70,C907839
33p,"C74,C75",C_0402_1005Metric,C1562
47p,"C22,C23",C_0402_1005Metric,C1567
1u,"C2,C3,C5,C7,C84,C9",C_0603_1608Metric,C15849
1n,"C24,C25,C26,C27,C28,C29,C30,C31,C32,C33,C34,C35,C36,C37,C38,C39",C_0603_1608Metric,C1588
680p,"C18,C19",C_0603_1608Metric,C1630
Micro_SD_Card,J10,microSD_HC_Wuerth_693072010801,C164170
MIC4427,"U42,U43,U44,U45",SO-8_3.9x4.9mm_P1.27mm,C171845
100,"R108,R109,R110,R111,R112,R113,R114,R115",R_0805_2012Metric,C17408
4.7k,"R103,R104,R105,R106,R107",R_0805_2012Metric,C17673
LMR14020,U3,SOIC-8-1EP_3.9x4.9mm_P1.27mm_EP2.29x3mm,C187824
4.7u,"C14,C4,C65,C66,C72,C76,C80,C82,C107",C_0603_1608Metric,C19666
1k,"RN10,RN5,RN6,RN7,RN8,RN9",R_Array_Convex_4x0603,C20197
Polyfuse,"F1,F2",R_1206_3216Metric,C207035
VNLD5090,"U1001,U1002,U1101,U1102,U1201,U1202",SOIC-8_3.9x4.9mm_P1.27mm,C222209
120,"R10,R101,R102,R7,R8,R9",R_0603_1608Metric,C22787
RED,D10,LED_0603_1608Metric_Castellated,C2286
82k,"R96,R116,R120",R_0603_1608Metric,C23254
2.2u,"C77,C78,C90",C_0603_1608Metric,C23630
1,R2,R_0402_1005Metric,C25086
330,"R91,R92,R93,R94,R95",R_0402_1005Metric,C25104
100k,"R13,R14,R19,R20,R98",R_0402_1005Metric,C25741
10k,"R1,R100,R3,R4,R47,R48,R49,R50,R59,R60,R61,R62,R71,R72,R73,R74,R83,R84,R85,R86,R89,R90,R97,R99,R117,R118,R119,R121,R123",R_0402_1005Metric,C25744
12k,"R17,R18,R5",R_0402_1005Metric,C25752
33k,"R11,R12,R21,R22",R_0402_1005Metric,C25779
470k,"R15,R16,R51,R52,R53,R54,R63,R64,R65,R66,R75,R76,R77,R78",R_0402_1005Metric,C25790
5.6k,"R43,R44,R45,R46,R55,R56,R57,R58,R67,R68,R69,R70,R79,R80,R81,R82",R_0402_1005Metric,C25908
10k,"RN1,RN11,RN2,RN3,RN4",R_Array_Convex_4x0603,C29718
SW_Push,"SW1,SW2",SW_SPST_EVQQ2,C318887
PSM712-LF-T7,IC1,SOT-23,C32677
68k,"R6,R122",R_0402_1005Metric,C36871
TLS115D0E,"U1,U2",Infineon_PG-DSO-8-43,C3747428
10u,"L2,L3",MWSA0503,C408412
MCP6004,"U15,U17,U19,U21,U7",TSSOP-14_4.4x5mm_P0.65mm,C50282
3.3n,"C16,C17",C_0805_2012Metric,C472819
MIC5205-3.3YM5,U41,SOT-23-5,C5370979
10n,"C100,C101,C102,C15,C8,C85,C86,C87,C88,C93,C94,C95,C96,C99",C_0603_1608Metric,C57112
AMS1117-3.3,U6,SOT-223-3_TabPin2,C6186
ORANGE,D13,LED_0603_1608Metric_Castellated,C2287
BLUE,D11,LED_0603_1608Metric_Castellated,C2288
GREEN,"D12,D9",LED_0603_1608Metric_Castellated,C12624
MCP2551-I-SN,"U4,U5",SOIC-8_3.9x4.9mm_P1.27mm,C7376
2.2u,L1,L_1210_3225Metric,C75646
BTS716G,U40,Infineon_PG-DSO-20-32,C85135
SRV05-4,"D15,U11,U12,U13,U16,U18,U20,U22",SOT-23-6,C85364
schottky,"D14,D16,D17,D6,D7,D8",D_SOD-123,C8598
D_Schottky,"D2,D3,D18",D_SMA,C8678
STM32H753ZIT6,U26,LQFP-144_20x20mm_P0.5mm,C730207
LPS25HBTR,U24,ST_HLGA-10_2.5x2.5mm_P0.6mm_LayoutBorder3x2y,C87898
47u_50V_Hybrid,"C1,C6",CP_Elec_8x10.5,C454346
S3225SMD32.768KOSC,U28,SMD3225-4P,C7431189
LM2733XMFX/NOPB,U46,SOT-23-5,C80169

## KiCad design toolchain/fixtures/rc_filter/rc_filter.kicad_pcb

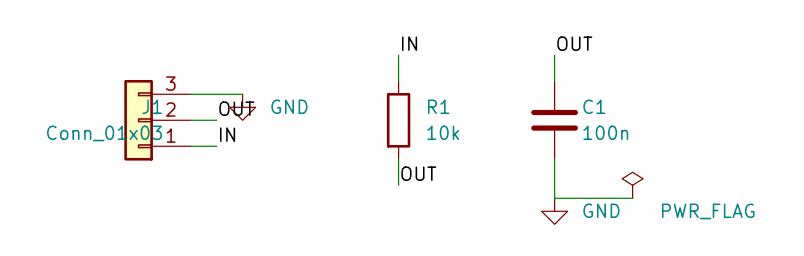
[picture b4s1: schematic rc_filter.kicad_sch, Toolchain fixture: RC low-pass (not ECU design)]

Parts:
C1: 100n; C_0805_2012Metric
J1: Conn_01x03; PinHeader_1x03_P2.54mm_Vertical
R1: 10k; R_0805_2012Metric

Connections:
/IN: J1.1, R1.1
/OUT: C1.1, J1.2, R1.2
GND: C1.2, J1.3

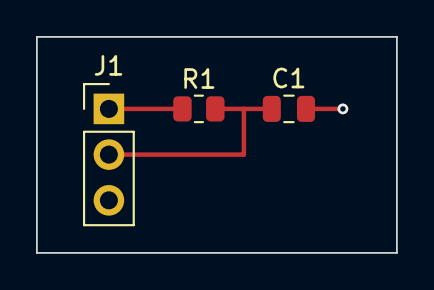
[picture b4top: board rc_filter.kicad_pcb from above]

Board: 2 copper layers, 20.0 x 12.0 mm, 3 parts (0 on the bottom side), 3 nets.

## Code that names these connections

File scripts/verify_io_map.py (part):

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        "Gpio::G6, // INJ2",
        "Gpio::G7, // INJ3",
        "Gpio::G8, // INJ4",
        "Gpio::B3,  // IGN1 / IGBT1",
        "Gpio::G15, // IGN2 / IGBT2",
        "Gpio::G14, // IGN3 / IGBT3",
        "Gpio::G13, // IGN4 / IGBT4",
        "engineConfiguration->idle.stepperStepPin = Gpio::B4;",
        "engineConfiguration->idle.stepperDirectionPin = Gpio::B7;",
        "engineConfiguration->stepperEnablePin = Gpio::B8;",
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        "Gpio getWifiCsPin()",
        "Gpio getWifiResetPin()",
        "Gpio getWifiIsrPin()",
        'efiSetPadMode("WBO1_NRST", Gpio::D4',
        'efiSetPadMode("WBO1_BOOT0", Gpio::D5',
        'efiSetPadMode("WBO2_NRST", Gpio::D6',
        'efiSetPadMode("WBO2_BOOT0", Gpio::D7',
    ]
    for snip in required_fw_snippets:
        if snip not in bcfg:
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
